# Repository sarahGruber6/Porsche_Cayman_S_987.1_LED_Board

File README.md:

Decorative board of Porsche with LEDs controlled by ATtiny1616 and powered by 3V CR2450. Modes cycle with button.

Board design is complete and will be ordered soon. I'll write some code for it then!

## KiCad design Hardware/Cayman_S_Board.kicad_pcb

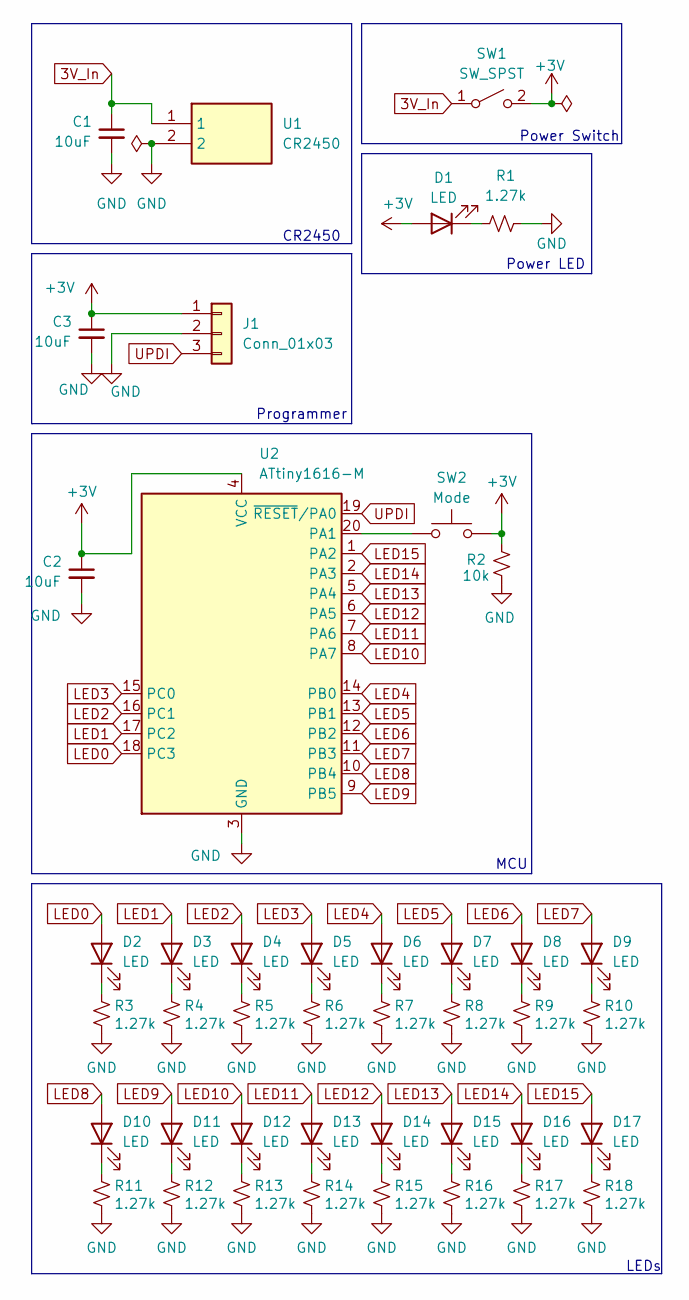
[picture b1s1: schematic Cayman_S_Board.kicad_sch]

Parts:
C1, C2, C3: 10uF; C_0805_2012Metric_Pad1.18x1.45mm_HandSolder
D1, D2, D3, D4, D5, D6, D7, D8, D9, D10, D11, D12, D13, D14, D15, D16, D17: LED; C_0603_1608Metric_Pad1.08x0.95mm_HandSolder
J1: Conn_01x03; PinSocket_1x03_P1.00mm_Vertical
R1, R3, R4, R5, R6, R7, R8, R9, R10, R11, R12, R13, R14, R15, R16, R17, R18: 1.27k; R_0603_1608Metric_Pad0.98x0.95mm_HandSolder
R2: 10k; R_0603_1608Metric_Pad0.98x0.95mm_HandSolder
SW1: SW_SPST; AS11CP
SW2: Mode; SW_PUSH-12mm
U1: CR2450; 79578211; Mouser Part Number 710-79578211
U2: ATtiny1616-M; VQFN-20-1EP_3x3mm_P0.4mm_EP1.7x1.7mm

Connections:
3V_In: C1.1, SW1.1 (A), U1.1
+3V: C2.1, C3.1, D1.2 (A), J1.1, R2.1, SW1.2 (B), SW2.2, U2.4 (VCC)
GND: C1.2, C2.2, C3.2, J1.2, R1.2, R2.2, R3.2, R4.2, R5.2, R6.2, R7.2, R8.2, R9.2, R10.2, R11.2, R12.2, R13.2, R14.2, R15.2, R16.2, R17.2, R18.2, U1.2, U2.3 (GND), U2.21 (GND)
LED0: D2.2 (A), U2.18 (PC3)
LED1: D3.2 (A), U2.17 (PC2)
LED2: D4.2 (A), U2.16 (PC1)
LED3: D5.2 (A), U2.15 (PC0)
LED4: D6.2 (A), U2.14 (PB0)
LED5: D7.2 (A), U2.13 (PB1)
LED6: D8.2 (A), U2.12 (PB2)
LED7: D9.2 (A), U2.11 (PB3)
LED8: D10.2 (A), U2.10 (PB4)
LED9: D11.2 (A), U2.9 (PB5)
LED10: D12.2 (A), U2.8 (PA7)
LED11: D13.2 (A), U2.7 (PA6)
LED12: D14.2 (A), U2.6 (PA5)
LED13: D15.2 (A), U2.5 (PA4)
LED14: D16.2 (A), U2.2 (PA3)
LED15: D17.2 (A), U2.1 (PA2)
unnamed: D1.1 (K), R1.1
unnamed: D2.1 (K), R3.1
unnamed: D3.1 (K), R4.1
unnamed: D4.1 (K), R5.1
unnamed: D5.1 (K), R6.1
unnamed: D6.1 (K), R7.1
unnamed: D7.1 (K), R8.1
unnamed: D8.1 (K), R9.1
unnamed: D9.1 (K), R10.1
unnamed: D10.1 (K), R11.1
unnamed: D11.1 (K), R12.1
unnamed: D12.1 (K), R13.1
unnamed: D13.1 (K), R14.1
unnamed: D14.1 (K), R15.1
unnamed: D15.1 (K), R16.1
unnamed: D16.1 (K), R17.1
unnamed: D17.1 (K), R18.1
unnamed: SW2.1, U2.20 (PA1)
UPDI: J1.3, U2.19 (~RESET/PA0)

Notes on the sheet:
MCU
CR2450
Power Switch
LEDs
Power LED
Programmer

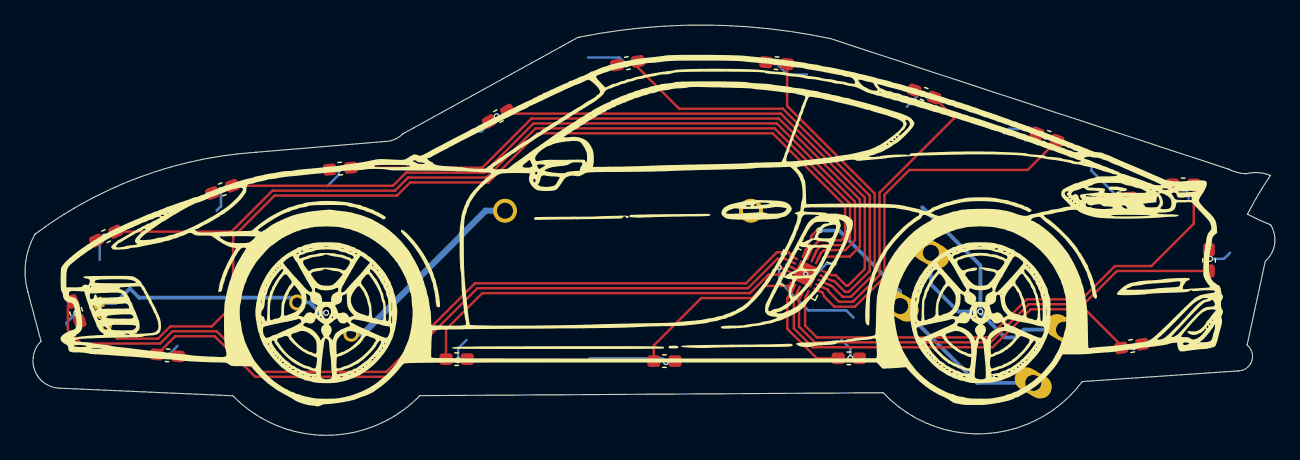
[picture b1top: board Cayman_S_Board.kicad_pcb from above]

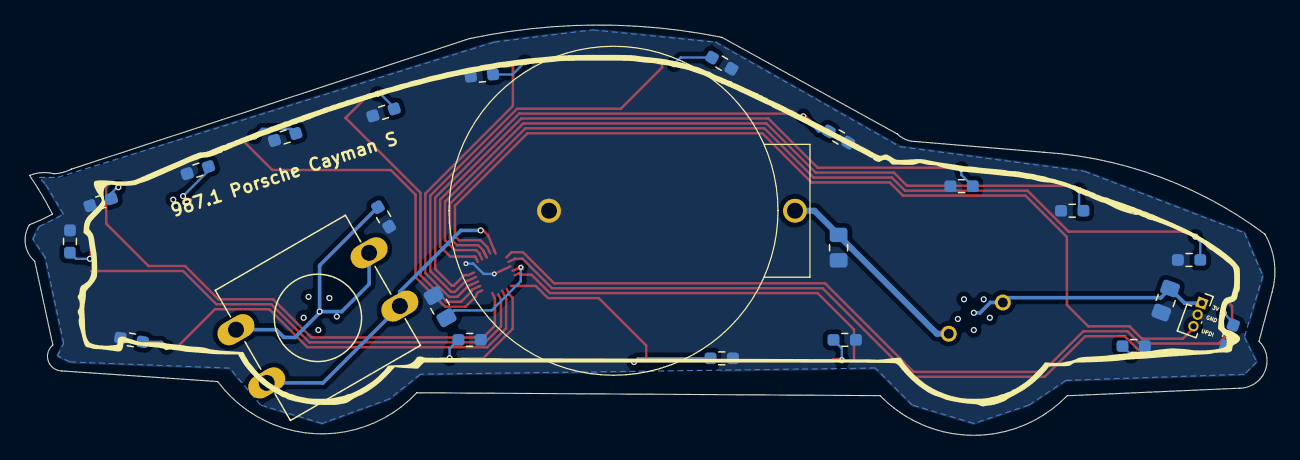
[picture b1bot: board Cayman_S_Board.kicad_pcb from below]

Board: 4 copper layers, 101.6 x 33.4 mm, 43 parts (25 on the bottom side), 38 nets.

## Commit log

2026-04-20 init, board design is complete, ordering soon and will write code once it gets here
2026-04-20 added some screenshots
2026-04-20 fixed md images
